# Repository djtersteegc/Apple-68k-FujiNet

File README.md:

Repo for early testing of FujiNet PCB's for 68k Apple Macs

# Rev0

Schematic - https://djtersteegc.github.io/Apple-68k-FujiNet/Apple-68k-FujiNet-Rev0-Schematic.pdf

Interactive BOM - https://djtersteegc.github.io/Apple-68k-FujiNet/ibom-Rev0.html

C1 and C2 can be considered optional, board should work without them.

You'll need 8.5mm high [2.54mm female header strips](https://www.aliexpress.us/item/2251832416528370.html) to mount the ESP32 and Pi Pico.  Buy the 1x40 versions and cut to length.

The switch controls power from the Mac DB19 port. Can be bridged via JP1 if you don't want to install and always be powered. The footprint also takes the common [**12D07VG4**](https://www.aliexpress.us/item/2255801015765871.html) you find on AliExpress.

MicroSD socket footprint is the common [Chinese push-push version](https://www.aliexpress.us/item/2251832613969983.html) used on all the FujiNet's to date.

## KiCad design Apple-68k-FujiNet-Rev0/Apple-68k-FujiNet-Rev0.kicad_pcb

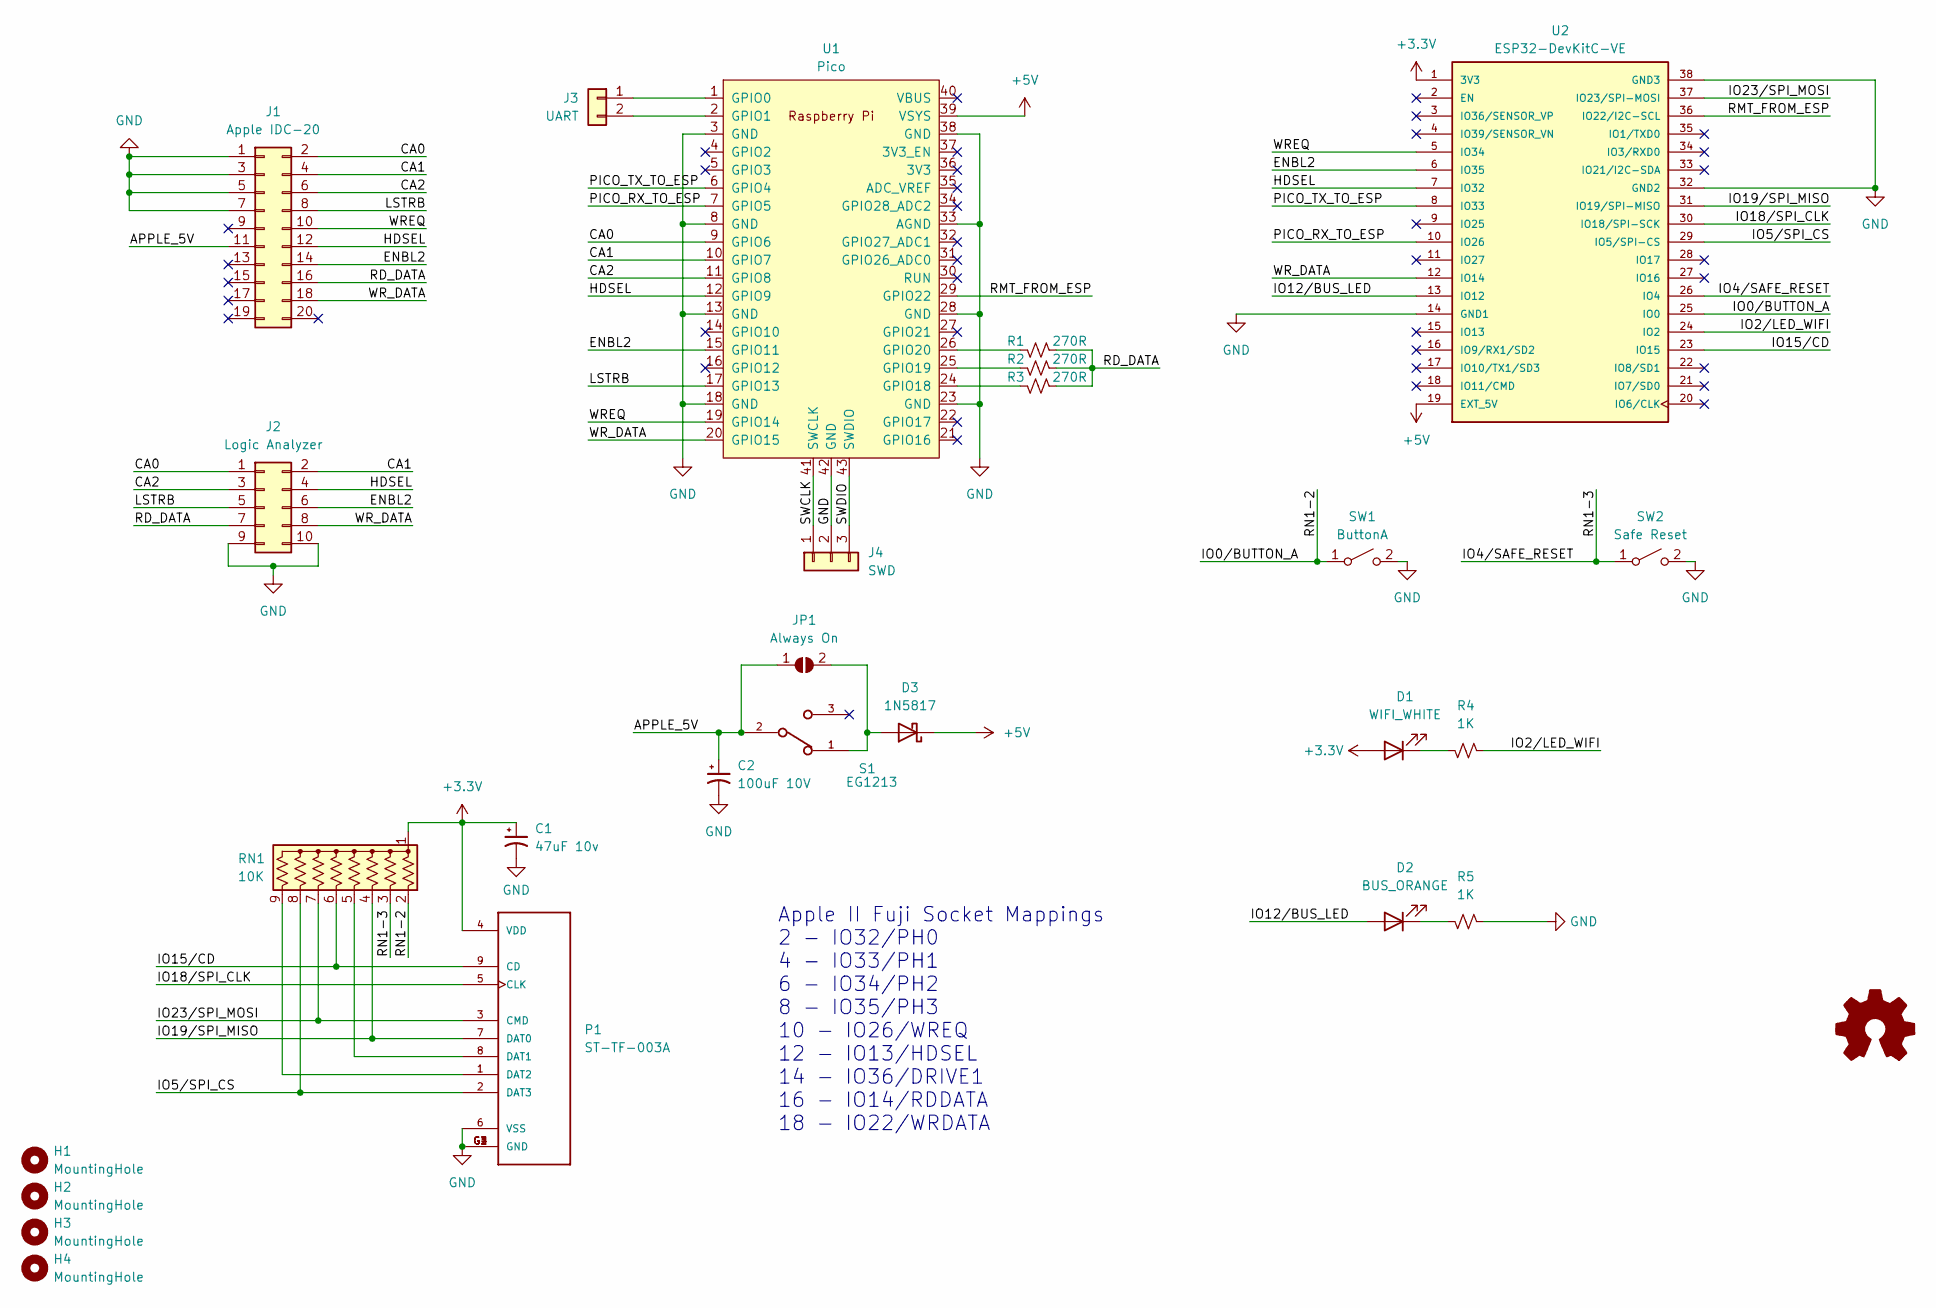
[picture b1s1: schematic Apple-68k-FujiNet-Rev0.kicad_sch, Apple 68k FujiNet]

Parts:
C1: 47uF 10v; CP_EIA-3528-15_AVX-H_Pad1.50x2.35mm_HandSolder
C2: 100uF 10V; CP_Radial_D6.3mm_P2.50mm
D1: WIFI_WHITE; LED_D5.0mm
D2: BUS_ORANGE; LED_D5.0mm
D3: 1N5817; D_DO-41_SOD81_P10.16mm_Horizontal
H1, H2, H3, H4: MountingHole; MountingHole_3.2mm_M3
J1: Apple IDC-20; IDC-Header_2x10_P2.54mm_Horizontal
J2: Logic Analyzer; PinHeader_2x05_P2.54mm_Vertical
J3: UART; PinHeader_1x02_P2.54mm_Vertical
J4: SWD; PinHeader_1x03_P2.54mm_Vertical
JP1: Always On; SolderJumper-2_P1.3mm_Open_RoundedPad1.0x1.5mm
P1: ST-TF-003A; SUNTECH_ST-TF-003A
R1, R2, R3: 270R; R_Axial_DIN0207_L6.3mm_D2.5mm_P7.62mm_Horizontal
R4, R5: 1K; R_Axial_DIN0207_L6.3mm_D2.5mm_P7.62mm_Horizontal
RN1: 10K; R_Array_SIP9
S1: EG1213; SW_EG1213
SW1: ButtonA; SW_PUSH_6mm_H5mm
SW2: Safe Reset; SW_PUSH_6mm_H5mm
U1: Pico; RPi_Pico_THT
U2: ESP32-DevKitC-VE; MODULE_ESP32-DEVKITC-32U; PARTREV N/A

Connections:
+3.3V: C1.1, D1.2 (A), P1.4 (VDD), RN1.1 (common), U2.1 (3V3)
+5V: D3.1 (K), U1.39 (VSYS), U2.19 (EXT_5V)
/APPLE_5V: C2.1, J1.11, JP1.1 (A), S1.2
/CA0: J1.2, J2.1, U1.9 (GPIO6)
/CA1: J1.4, J2.2, U1.10 (GPIO7)
/CA2: J1.6, J2.3, U1.11 (GPIO8)
/ENBL2: J1.14, J2.6, U1.15 (GPIO11), U2.6 (IO35)
/HDSEL: J1.12, J2.4, U1.12 (GPIO9), U2.7 (IO32)
/IO0/BUTTON_A: RN1.2 (R1), SW1.1 (A), U2.25 (IO0)
/IO2/LED_WIFI: R4.2, U2.24 (IO2)
/IO4/SAFE_RESET: RN1.3 (R2), SW2.1 (A), U2.26 (IO4)
/IO5/SPI_CS: P1.2 (DAT3), RN1.8 (R7), U2.29 (IO5/SPI-CS)
/IO12/BUS_LED: D2.2 (A), U2.13 (IO12)
/IO15/CD: P1.9 (CD), RN1.6 (R5), U2.23 (IO15)
/IO18/SPI_CLK: P1.5 (CLK), U2.30 (IO18/SPI-SCK)
/IO19/SPI_MISO: P1.7 (DAT0), RN1.4 (R3), U2.31 (IO19/SPI-MISO)
/IO23/SPI_MOSI: P1.3 (CMD), RN1.7 (R6), U2.37 (IO23/SPI-MOSI)
/LSTRB: J1.8, J2.5, U1.17 (GPIO13)
/PICO_RX_TO_ESP: U1.7 (GPIO5), U2.10 (IO26)
/PICO_TX_TO_ESP: U1.6 (GPIO4), U2.8 (IO33)
/RD_DATA: J1.16, J2.7, R1.2, R2.2, R3.2
/RMT_FROM_ESP: U1.29 (GPIO22), U2.36 (IO22/I2C-SCL)
/SWCLK: J4.1, U1.41 (SWCLK)
/SWDIO: J4.3, U1.43 (SWDIO)
/WREQ: J1.10, U1.19 (GPIO14), U2.5 (IO34)
/WR_DATA: J1.18, J2.8, U1.20 (GPIO15), U2.12 (IO14)
GND: C1.2, C2.2, J1.1, J1.3, J1.5, J1.7, J2.9, J2.10, J4.2, P1.6 (VSS), P1.G1 (GND), P1.G2 (GND), P1.G3 (GND), P1.G4 (GND), R5.2, SW1.2 (B), SW2.2 (B), U1.3 (GND), U1.8 (GND), U1.13 (GND), U1.18 (GND), U1.23 (GND), U1.28 (GND), U1.33 (AGND), U1.38 (GND), U1.42 (GND), U2.14 (GND1), U2.32 (GND2), U2.38 (GND3)
unnamed: D1.1 (K), R4.1
unnamed: D2.1 (K), R5.1
unnamed: D3.2 (A), JP1.2 (B), S1.1
unnamed: J3.1, U1.1 (GPIO0)
unnamed: J3.2, U1.2 (GPIO1)
unnamed: P1.8 (DAT1), RN1.5 (R4)
unnamed: P1.1 (DAT2), RN1.9 (R8)
unnamed: R3.1, U1.24 (GPIO18)
unnamed: R2.1, U1.25 (GPIO19)
unnamed: R1.1, U1.26 (GPIO20)

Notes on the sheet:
Apple II Fuji Socket Mappings 2 - IO32/PH0 4 - IO33/PH1 6 - IO34/PH2 8 - IO35/PH3 10 - IO26/WREQ 12 - IO13/HDSEL 14 - IO36/DRIVE1 16 - IO14/RDDATA 18 - IO22/WRDATA

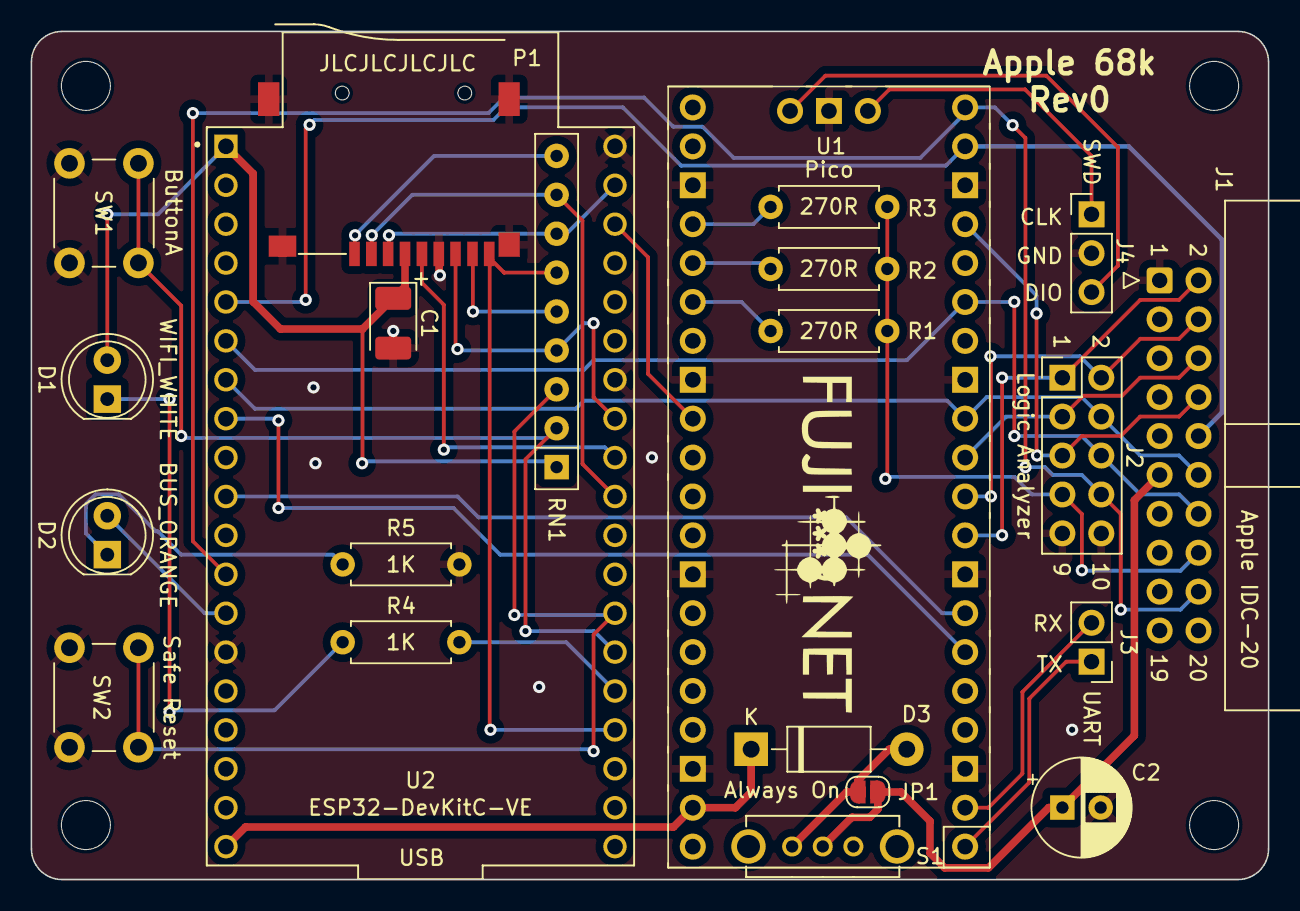
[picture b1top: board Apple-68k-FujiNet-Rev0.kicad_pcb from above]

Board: 2 copper layers, 80.8 x 55.4 mm, 26 parts (0 on the bottom side), 37 nets.

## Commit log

2024-01-20 Rev0
2024-01-20 Remove ground on Pin 7 for Rev0 boards since Jeff may also use these for Apple II development
2024-01-20 Update Schematic to remove GND on pin 7
2024-01-20 Add 3D board renders for assembly guidance
2024-02-09 Initial stab at a case for Rev0
2024-02-16 Tweak clearances, add button options, add new body with cutout for headers and modules buttons
